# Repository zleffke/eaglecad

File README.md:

# eagle --OBSOLETE--
EagleCAD schematics, boards, and libraries

## --OBSOLETE--

The projects in this repository have been moved to their own stand alone repositories.  Finally decided it was dumb to have everything in one repo, because if anyone else actually wants to use one thing, they would have to clone everything.

The files in this repo will no longer be updated and new projects will be created in their own repo.  This repo is not being nuked for the moment and is being kept around as an archival repo in case I forgot to move something over to its own repo.  Eventually, this will get nuked.

## -------------

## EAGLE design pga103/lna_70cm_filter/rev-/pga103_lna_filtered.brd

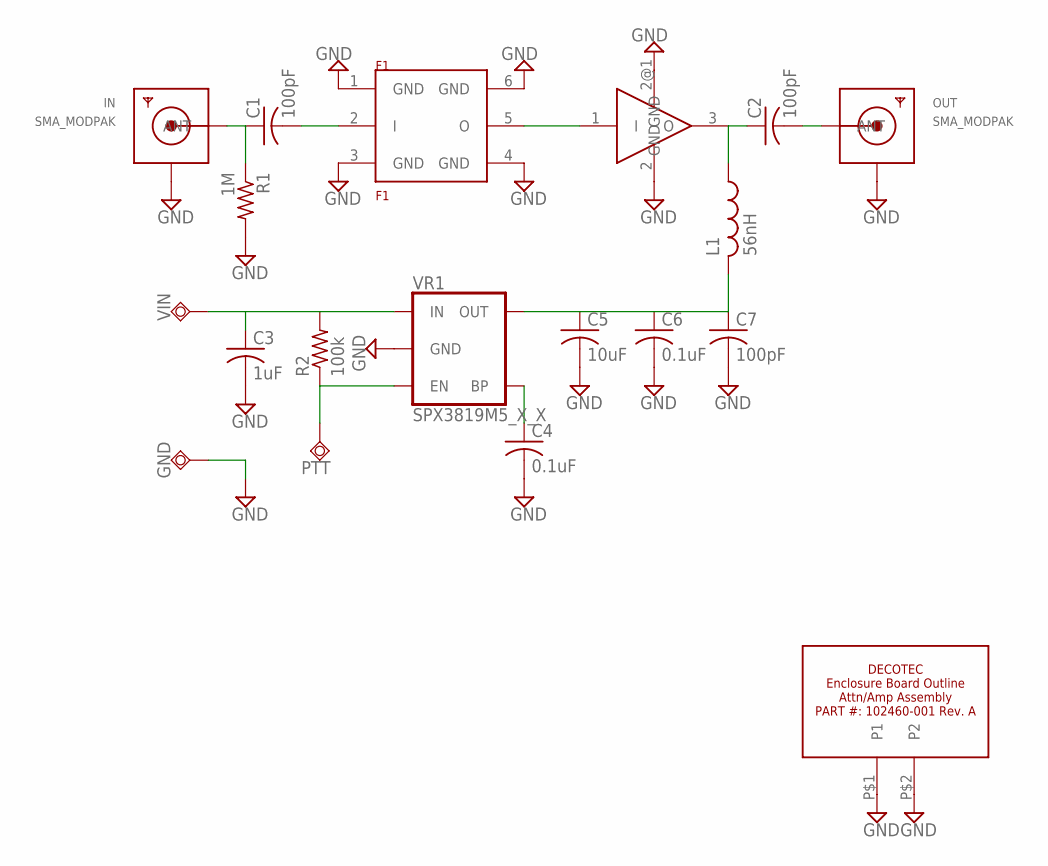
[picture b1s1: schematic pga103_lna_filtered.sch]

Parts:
A1: PGA-103+; SOT89
C1, C2, C7: 100pF; C0805K
C3: 1uF; C0805K
C4, C6: 0.1uF; C0805K
C5: 10uF; C0805K
F1: F1; SM3030-6
GND: TPSQTP20SQ; TP20SQ
IN: SMA_MODPAK; SMA_MODPAK_V1
L1: 56nH; C0805K
OUT: SMA_MODPAK; SMA_MODPAK_V1
PTT: TPSQTP20SQ; TP20SQ
R1: 1M; R0805
R2: 100k; R0805
U$1: DECOTEC_102460-001A
VIN: TPSQTP20SQ; TP20SQ
VR1: SPX3819M5_X_X; SOT23-5

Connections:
GND: A1.2 (GND), A1.2@1 (GND), C3.2, C4.2, C5.2, C6.2, C7.2, F1.1 (GND), F1.3 (GND), F1.4 (GND), F1.6 (GND), GND.TP, IN.GND@1 (GND1), OUT.GND@1 (GND1), R1.2, U$1.P$1 (P1), U$1.P$2 (P2), VR1.2 (GND)
unnamed: C1.1, IN.P (ANT), R1.1
unnamed: C1.2, F1.2 (I)
unnamed: C2.2, OUT.P (ANT)
unnamed: A1.3 (O), C2.1, L1.1
unnamed: A1.1 (I), F1.5 (O)
unnamed: C5.1, C6.1, C7.1, L1.2, VR1.5 (OUT)
unnamed: C4.1, VR1.4 (BP)
PTT: PTT.TP, R2.1, VR1.3 (EN)
VIN: C3.1, R2.2, VIN.TP, VR1.1 (IN)

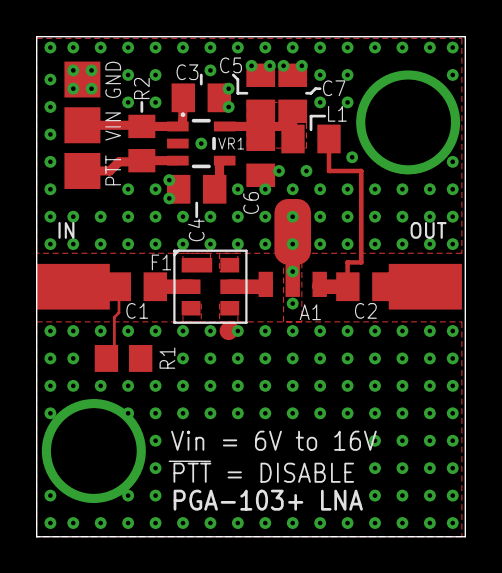
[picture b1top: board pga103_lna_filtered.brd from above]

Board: 2 copper layers, 23.8 x 27.8 mm, 19 parts (0 on the bottom side), 10 nets.

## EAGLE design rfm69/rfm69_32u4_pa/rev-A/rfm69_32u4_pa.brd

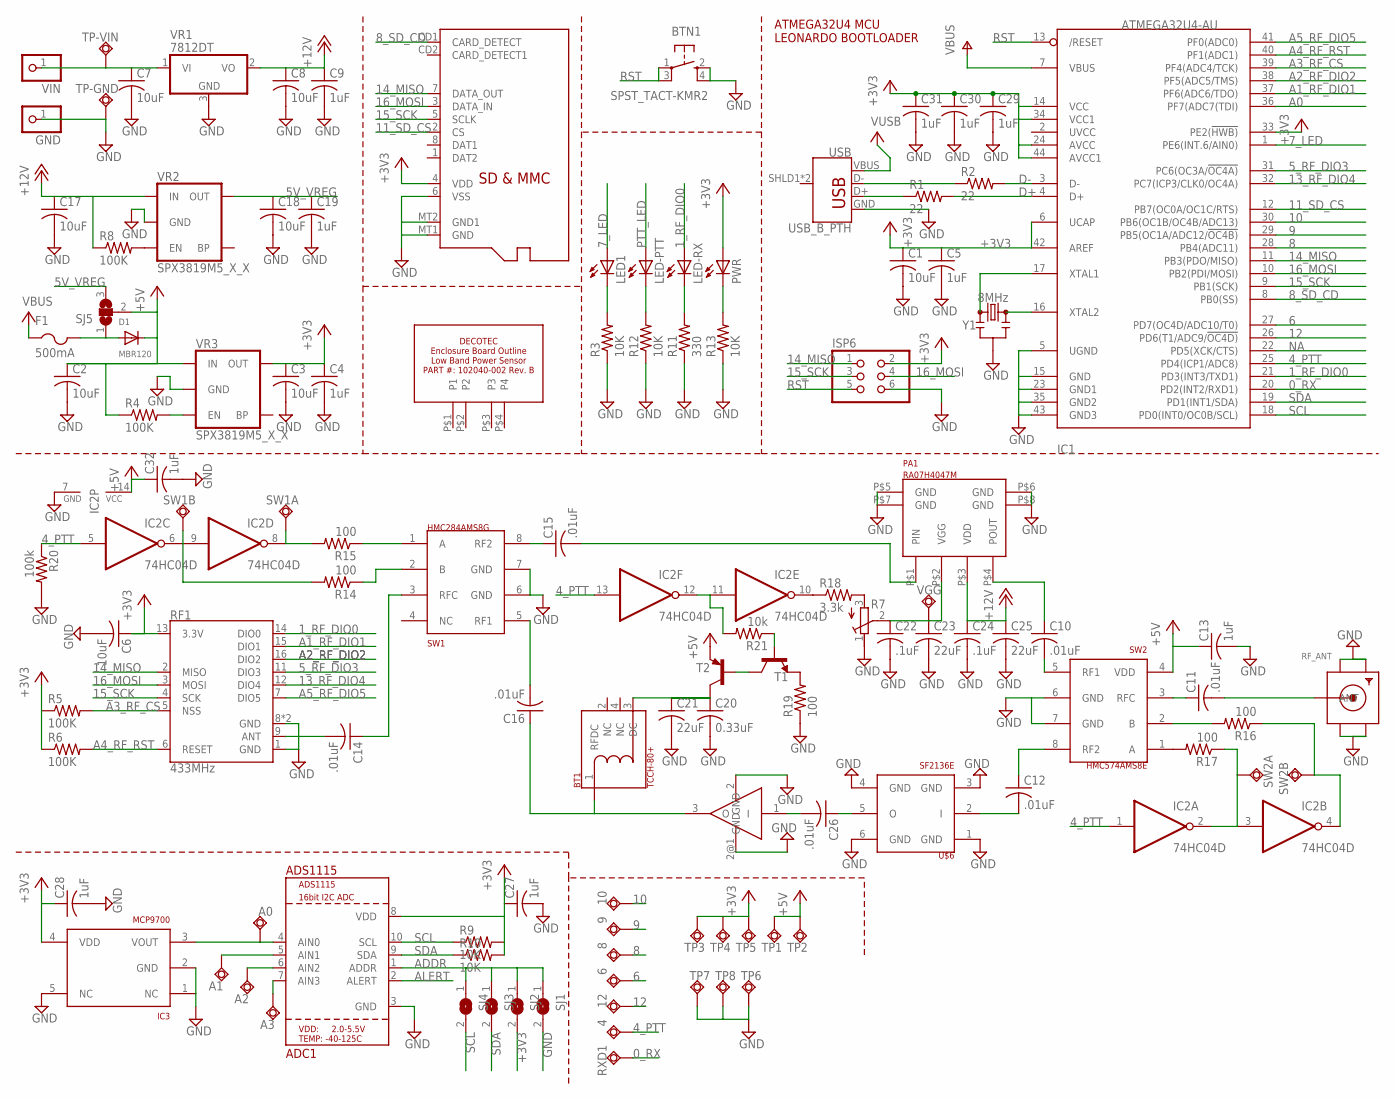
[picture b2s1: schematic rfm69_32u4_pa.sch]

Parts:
4, 6, 8, 9, 10, 12: TPSQTP10SQ; TP10SQ
A0, A1, A2, A3: TPSQTP10SQ; TP10SQ
ADC1: ADS1115; MSOP10
BT1: TCCH-80+
BTN1: SPST_TACT-KMR2; KMR2
C1, C2, C3, C6, C7, C8, C17, C18: 10uF; C0805K
C4, C5, C9, C13, C19, C27, C28, C29, C30, C31, C32: 1uF; C0805K
C10, C11, C12, C14, C15, C16, C26: .01uF; C0805K
C20: 0.33uF; C0805K
C21, C23, C25: 22uF; C0805K
C22, C24: .1uF; C0805K
D1: MBR120; SOD-123
F1: 500mA; R1206
GND: PINHD-1X1; 1X01
IC1: ATMEGA32U4-AU; TQFP44
IC2: 74HC04D; SO14
IC3: MCP9700; SC70
ISP6: PINHD-2X3; 2X03
LED1: LEDCHIPLED_0805; CHIPLED_0805
LED-PTT: LEDCHIPLED_0805; CHIPLED_0805
LED-RX: LEDCHIPLED_0805; CHIPLED_0805
PA1: RA07H4047M; H46
PGA-103+: PGA-103+; SOT89
PWR: LEDCHIPLED_0805; CHIPLED_0805
R1, R2: 22; R0805
R3, R9, R10, R12, R13: 10K; R0805
R4, R5, R6, R8: 100K; R0805
R7: R-TRIMM3314G; RTRIM3314G
R11: 330; R0805
R14, R15, R16, R17, R19: 100; R0805
R18: 3.3k; R0805
R20: 100k; R0805
R21: 10k; R0805
RF1: 433MHz; RFM69HCW-XXXS2
RF_ANT: SMACONNECTOR_EDGE; SMA_EDGELAUNCH
RXD1: TPSQTP10SQ; TP10SQ
SJ1, SJ2, SJ3, SJ4: SJ
SJ5: SJ2W; SJ_2
SW1: HMC284AMS8G; MSOP8
SW1A, SW1B, SW2A, SW2B: TPSQTP10SQ; TP10SQ
SW2: HMC574AMS8E; MSOP8
T1: MMBT3904LT1-NPN-SOT23-BEC; SOT23-BEC
T2: MMBT3906LT1-PNP-SOT23-BEC; SOT23-BEC
TP1, TP2, TP3, TP4, TP5, TP6, TP7, TP8: TPSQTP10SQ; TP10SQ
TP-GND: TPSQTP20SQ; TP20SQ
TP-VIN: TPSQTP20SQ; TP20SQ
U$2: DECOTEC_102040-002B
U$3: MICROSD
U$6: SF2136E; SM3030-6
USB: USB_B_PTH; USB-B-PTH
VGG: TPSQTP10SQ; TP10SQ
VIN: PINHD-1X1; 1X01
VR1: 7812DT; TO252
VR2, VR3: SPX3819M5_X_X; SOT23-5
Y1: 8MHz; RESONATOR-SMD-3.2X1.3

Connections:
0_RX: IC1.20 (PD2(INT2/RXD1)), RXD1.TP
1_RF_DIO0: IC1.21 (PD3(INT3/TXD1)), LED-RX.A, RF1.14 (DIO0)
4_PTT: 4.TP, IC1.25 (PD4(ICP1/ADC8)), IC2.1 (I), IC2.5 (I), IC2.13 (I), R20.1
5V_VREG: C18.1, C19.1, SJ5.3, VR2.5 (OUT)
5_RF_DIO3: IC1.31 (PC6(OC3A/!OC4A)), RF1.11 (DIO3)
6: 6.TP, IC1.27 (PD7(OC4D/ADC10/T0))
7_LED: IC1.1 (PE6(INT.6/AIN0)), LED1.A
8: 8.TP, IC1.28 (PB4(ADC11))
8_SD_CD: IC1.8 (PB0(SS)), U$3.CD1 (CARD_DETECT)
9: 9.TP, IC1.29 (PB5(OC1A/ADC12/!OC4B))
10: 10.TP, IC1.30 (PB6(OC1B/OC4B/ADC13))
11_SD_CS: IC1.12 (PB7(OC0A/OC1C/RTS)), U$3.2 (CS)
12: 12.TP, IC1.26 (PD6(T1/ADC9/!OC4D))
13_RF_DIO4: IC1.32 (PC7(ICP3/CLK0/OC4A)), RF1.12 (DIO4)
14_MISO: IC1.11 (PB3(PDO/MISO)), ISP6.1, RF1.2 (MISO), U$3.7 (DATA_OUT)
15_SCK: IC1.9 (PB1(SCK)), ISP6.3, RF1.4 (SCK), U$3.5 (SCLK)
16_MOSI: IC1.10 (PB2(PDI/MOSI)), ISP6.4, RF1.3 (MOSI), U$3.3 (DATA_IN)
+3V3: ADC1.8 (VDD), C1.1, C3.1, C4.1, C5.1, C6.1, C27.1, C28.1, C29.1, C30.1, C31.1, IC1.6 (UCAP), IC1.14 (VCC), IC1.24 (AVCC), IC1.33 (PE2(!HWB)), IC1.34 (VCC1), IC1.42 (AREF), IC1.44 (AVCC1), IC3.4 (VDD), ISP6.2, PWR.A, R5.1, R6.1, R9.2, R10.2, RF1.13 (3.3V), SJ2.2, TP3.TP, TP4.TP, TP5.TP, U$3.4 (VDD), VR3.5 (OUT)
+5V: C2.1, C13.1, C32.1, D1.C, IC2.14 (VCC), R4.1, SJ5.2, SW2.4 (VDD), T2.E, TP1.TP, TP2.TP, VR3.1 (IN)
+12V: C8.1, C9.1, C17.1, C24.1, C25.1, PA1.P$3 (VDD), R8.1, VR1.2 (VO), VR2.1 (IN)
A0: IC1.36 (PF7(ADC7(TDI))
A1_RF_DIO1: IC1.37 (PF6(ADC6/TDO)), RF1.15 (DIO1)
A2_RF_DIO2: IC1.38 (PF5(ADC5/TMS)), RF1.16 (DIO2)
A3_RF_CS: IC1.39 (PF4(ADC4/TCK)), R5.2, RF1.5 (NSS)
A4_RF_RST: IC1.40 (PF1(ADC1)), R6.2, RF1.6 (RESET)
A5_RF_DIO5: IC1.41 (PF0(ADC0)), RF1.7 (DIO5)
ADDR: ADC1.1 (ADDR), SJ1.1, SJ2.1, SJ3.1, SJ4.1
AIN1: A1.TP, ADC1.5 (AIN1)
AIN2: A2.TP, ADC1.6 (AIN2)
AIN3: A3.TP, ADC1.7 (AIN3)
ALERT: ADC1.2 (ALERT)
ANT: C14.2, RF1.9 (ANT)
D+: IC1.4 (D+), R1.2
D-: IC1.3 (D-), R2.2
EN: R4.2, VR3.3 (EN)
GND: ADC1.3 (GND), BTN1.2 (S), BTN1.4 (S1), C1.2, C2.2, C3.2, C4.2, C5.2, C6.2, C7.2, C8.2, C9.2, C13.2, C17.2, C18.2, C19.2, C20.2, C21.2, C22.2, C23.2, C24.2, C25.2, C27.2, C28.2, C29.2, C30.2, C31.2, C32.2, GND.1, IC1.5 (UGND), IC1.15 (GND), IC1.23 (GND1), IC1.35 (GND2), IC1.43 (GND3), IC2.7 (GND), IC3.1 (NC), IC3.2 (GND), IC3.5 (NC), ISP6.6, PA1.P$5 (GND), PA1.P$6 (GND), PA1.P$7 (GND), PA1.P$8 (GND), PGA-103+.2 (GND), PGA-103+.2@1 (GND), R3.1, R7.1 (E), R11.1, R12.1, R13.1, R19.1, R20.2, RF1.1 (GND), RF1.8 (GND), RF1.10 (GND), RF_ANT.GND@1 (GND4), RF_ANT.GND@2 (GND3), RF_ANT.GND@3 (GND2), RF_ANT.GND@4 (GND1), SJ1.2, SW1.6 (GND), SW1.7 (GND), SW2.6 (GND), SW2.7 (GND), TP6.TP, TP7.TP, TP8.TP, TP-GND.TP, U$3.6 (VSS), U$3.MT1 (GND), U$3.MT2 (GND1), U$6.1 (GND), U$6.3 (GND), U$6.4 (GND), U$6.6 (GND), USB.GND, VR1.3 (GND), VR2.2 (GND), VR3.2 (GND), Y1.2
unnamed: R1.1, USB.D+
unnamed: LED1.C, R3.2
unnamed: R2.1, USB.D-
unnamed: C15.2, PA1.P$1 (PIN)
unnamed: C10.1, PA1.P$4 (POUT)
unnamed: C10.2, SW2.5 (RF1)
unnamed: LED-PTT.C, R12.2
unnamed: PWR.C, R13.2
unnamed: C26.1, U$6.5 (O)
unnamed: C11.2, RF_ANT.P (ANT)
unnamed: C11.1, SW2.3 (RFC)
unnamed: C14.1, SW1.3 (RFC)
unnamed: C15.1, SW1.8 (RF2)
unnamed: C16.2, SW1.5 (RF1)
unnamed: R14.1, SW1.2 (B)
unnamed: BT1.1 (RFDC), C16.1, PGA-103+.3 (O)
unnamed: C22.1, C23.1, PA1.P$2 (VGG), R7.2 (S), VGG.TP
unnamed: C12.1, SW2.8 (RF2)
unnamed: C12.2, U$6.2 (I)
unnamed: R15.1, SW1.1 (A)
unnamed: C26.2, PGA-103+.1 (I)
unnamed: R8.2, VR2.3 (EN)
unnamed: LED-RX.C, R11.2
unnamed: R17.2, SW2.1 (A)
unnamed: R16.2, SW2.2 (B)
unnamed: IC2.11 (I), IC2.12 (O), R21.2
unnamed: R7.3 (A), R18.2
unnamed: T1.C, T2.B
unnamed: BT1.3 (DC), C20.1, C21.1, T2.C
unnamed: R19.2, T1.E
unnamed: R21.1, T1.B
NA: IC1.22 (PD5(XCK/CTS))
PTT_LED: IC2.10 (O), LED-PTT.A, R18.1
RST: BTN1.1, BTN1.3 (P1), IC1.13 (/RESET), ISP6.5
SCL: ADC1.10 (SCL), IC1.18 (PD0(INT0/OC0B/SCL)), R9.1, SJ4.2
SDA: ADC1.9 (SDA), IC1.19 (PD1(INT1/SDA)), R10.1, SJ3.2
SW1A: IC2.8 (O), R15.2, SW1A.TP
SW1B: IC2.6 (O), IC2.9 (I), R14.2, SW1B.TP
SW2A: IC2.2 (O), IC2.3 (I), R17.1, SW2A.TP
SW2B: IC2.4 (O), R16.1, SW2B.TP
VBUS: D1.A, F1.2, IC1.7 (VBUS), SJ5.1
VIN: C7.1, TP-VIN.TP, VIN.1, VR1.1 (VI)
VUSB: F1.1, USB.VBUS
V_PA_TEMP: A0.TP, ADC1.4 (AIN0), IC3.3 (VOUT)
XTAL1: IC1.17 (XTAL1), Y1.1
XTAL2: IC1.16 (XTAL2), Y1.3

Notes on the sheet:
ATMEGA32U4 MCU LEONARDO BOOTLOADER

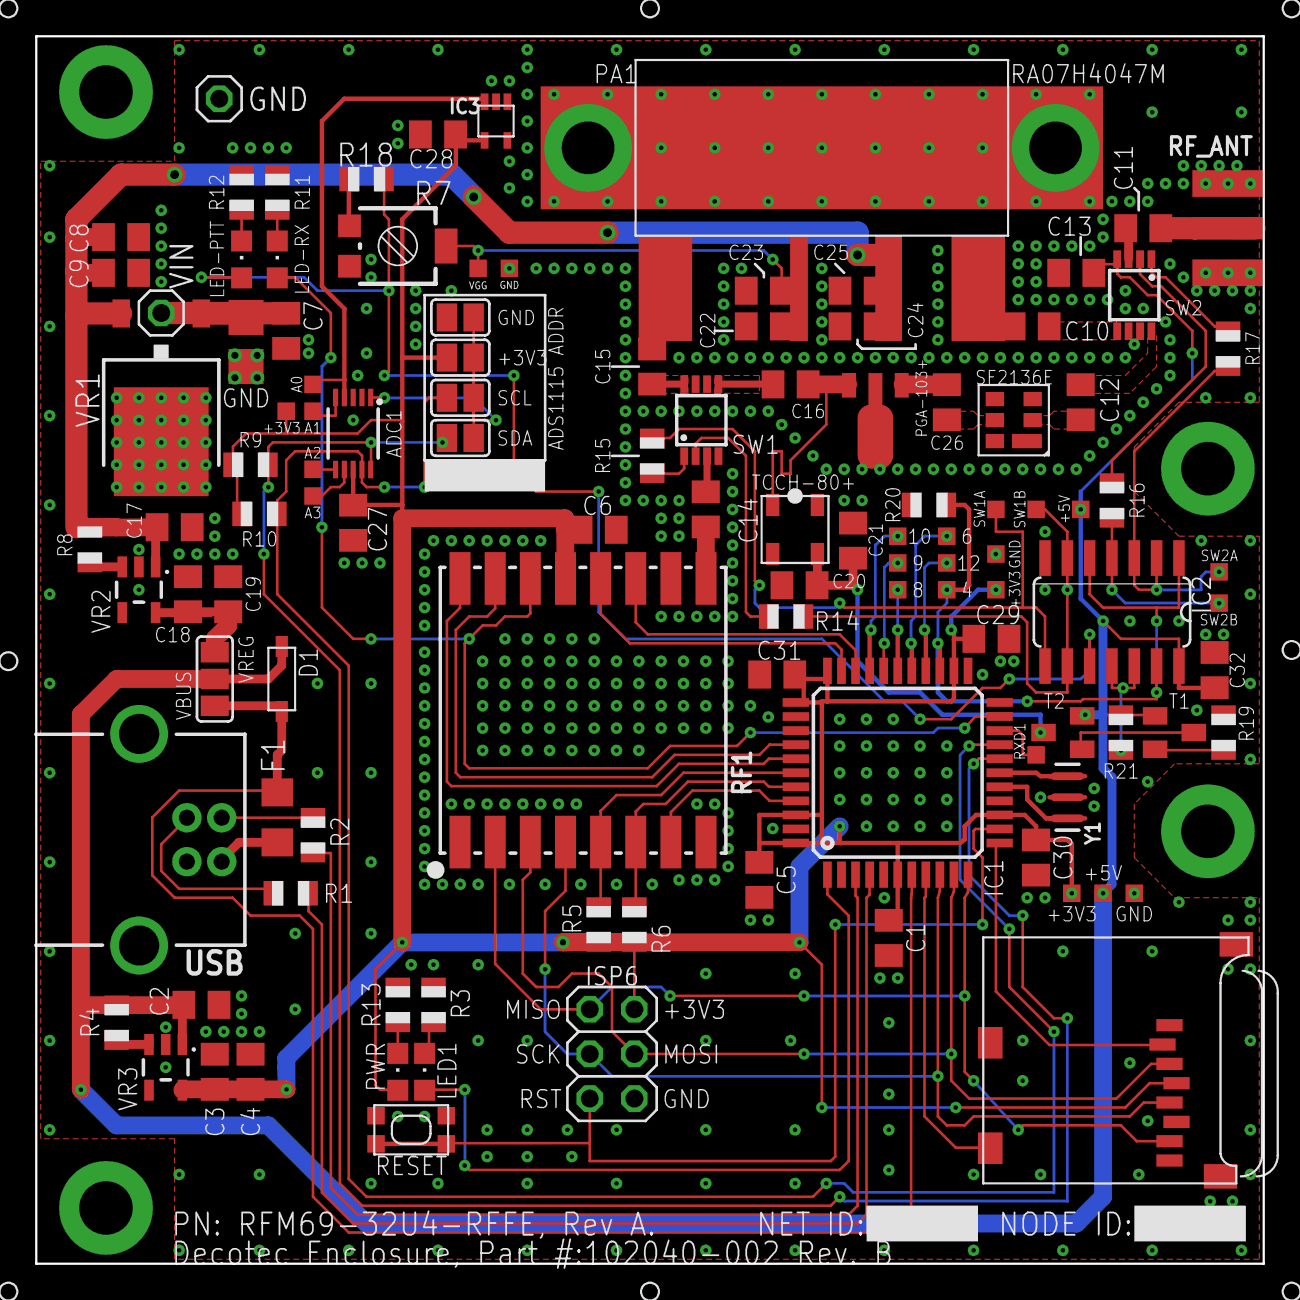
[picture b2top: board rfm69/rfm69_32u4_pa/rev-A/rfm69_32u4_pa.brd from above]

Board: 2 copper layers, 69.8 x 69.8 mm, 115 parts (0 on the bottom side), 79 nets.

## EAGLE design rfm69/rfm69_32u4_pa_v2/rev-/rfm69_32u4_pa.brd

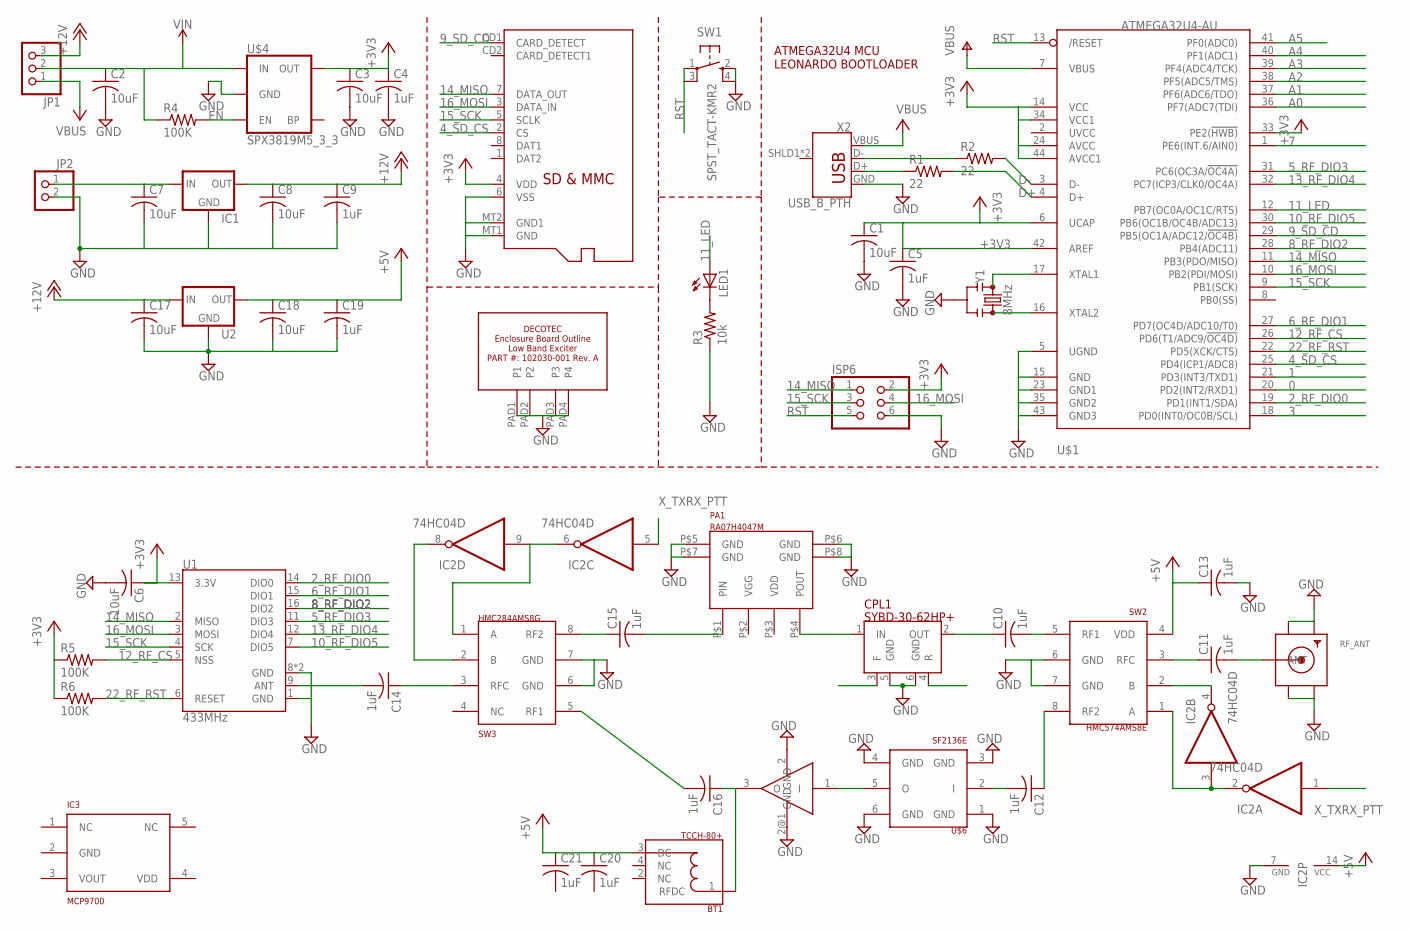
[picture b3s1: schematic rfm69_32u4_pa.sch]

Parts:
BT1: TCCH-80+
C1, C2, C3, C6, C7, C8, C17, C18: 10uF; C0805K
C4, C5, C9, C10, C11, C12, C13, C14, C15, C16, C19, C20, C21: 1uF; C0805K
CPL1: SYBD-30-62HP+
IC1: 78XXL
IC2: 74HC04D; SO14
IC3: MCP9700; SC70
ISP6: PINHD-2X3; 2X03
JP1: PINHD-1X3; 1X03
JP2: PINHD-1X2; 1X02
LED1: LEDCHIPLED_0805; CHIPLED_0805
PA1: RA07H4047M; H46
R1, R2: 22; R0805
R3: 10k; R0805
R4, R5, R6: 100K; R0805
RF_ANT: SMACONNECTOR_EDGE; SMA_EDGELAUNCH
SW1: SPST_TACT-KMR2; KMR2
SW2: HMC574AMS8E; MSOP8
SW3: HMC284AMS8G; MSOP8
U1: 433MHz; RFM69HCW-XXXS2
U2: V_REG_78XX-TO-220; TO-220-ALT
U$1: ATMEGA32U4-AU; TQFP44
U$2: DECOTEC_102030-001A
U$3: MICROSD
U$4: SPX3819M5_3_3; SOT23-5
U$5: PGA-103+; SOT89
U$6: SF2136E; SM3030-6
X2: USB_B_PTH; USB-B-PTH
Y1: 8MHz; RESONATOR-SMD-3.2X1.3

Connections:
0: U$1.20 (PD2(INT2/RXD1))
1: U$1.21 (PD3(INT3/TXD1))
2_RF_DIO0: U1.14 (DIO0), U$1.19 (PD1(INT1/SDA))
3: U$1.18 (PD0(INT0/OC0B/SCL))
4_SD_CS: U$1.25 (PD4(ICP1/ADC8)), U$3.2 (CS)
5_RF_DIO3: U1.11 (DIO3), U$1.31 (PC6(OC3A/!OC4A))
6_RF_DIO1: U1.15 (DIO1), U$1.27 (PD7(OC4D/ADC10/T0))
7: U$1.1 (PE6(INT.6/AIN0))
8_RF_DIO2: U1.16 (DIO2), U$1.28 (PB4(ADC11))
9_SD_CD: U$1.29 (PB5(OC1A/ADC12/!OC4B)), U$3.CD1 (CARD_DETECT)
10_RF_DIO5: U1.7 (DIO5), U$1.30 (PB6(OC1B/OC4B/ADC13))
11_LED: LED1.A, U$1.12 (PB7(OC0A/OC1C/RTS))
12_RF_CS: R5.2, U1.5 (NSS), U$1.26 (PD6(T1/ADC9/!OC4D))
13_RF_DIO4: U1.12 (DIO4), U$1.32 (PC7(ICP3/CLK0/OC4A))
14_MISO: ISP6.1, U1.2 (MISO), U$1.11 (PB3(PDO/MISO)), U$3.7 (DATA_OUT)
15_SCK: ISP6.3, U1.4 (SCK), U$1.9 (PB1(SCK)), U$3.5 (SCLK)
16_MOSI: ISP6.4, U1.3 (MOSI), U$1.10 (PB2(PDI/MOSI)), U$3.3 (DATA_IN)
22_RF_RST: R6.2, U1.6 (RESET), U$1.22 (PD5(XCK/CTS))
+3V3: C1.1, C3.1, C4.1, C5.1, C6.1, ISP6.2, R5.1, R6.1, U1.13 (3.3V), U$1.6 (UCAP), U$1.14 (VCC), U$1.24 (AVCC), U$1.33 (PE2(!HWB)), U$1.34 (VCC1), U$1.42 (AREF), U$1.44 (AVCC1), U$3.4 (VDD), U$4.5 (OUT)
+5V: BT1.3 (DC), C13.1, C18.1, C19.1, C20.1, C21.1, IC2.14 (VCC), SW2.4 (VDD), U2.OUT
+12V: C8.1, C9.1, C17.1, IC1.OUT, JP1.3, U2.IN
A0: U$1.36 (PF7(ADC7(TDI))
A1: U$1.37 (PF6(ADC6/TDO))
A2: U$1.38 (PF5(ADC5/TMS))
A3: U$1.39 (PF4(ADC4/TCK))
A4: U$1.40 (PF1(ADC1))
A5: U$1.41 (PF0(ADC0))
ANT: C14.2, U1.9 (ANT)
CPL_FWD: CPL1.3 (F)
CPL_REV: CPL1.4 (R)
D+: R1.2, U$1.4 (D+)
D-: R2.2, U$1.3 (D-)
EN: R4.2, U$4.3 (EN)
GND: C1.2, C2.2, C3.2, C4.2, C5.2, C6.2, C7.2, C8.2, C9.2, C13.2, C17.2, C18.2, C19.2, CPL1.5 (GND), CPL1.6 (GND), IC1.GND, IC2.7 (GND), ISP6.6, JP2.2, PA1.P$5 (GND), PA1.P$6 (GND), PA1.P$7 (GND), PA1.P$8 (GND), R3.1, RF_ANT.GND@1 (GND4), RF_ANT.GND@2 (GND3), RF_ANT.GND@3 (GND2), RF_ANT.GND@4 (GND1), SW1.2 (S), SW1.4 (S1), SW2.6 (GND), SW2.7 (GND), SW3.6 (GND), SW3.7 (GND), U1.1 (GND), U1.8 (GND), U1.10 (GND), U2.GND, U$1.5 (UGND), U$1.15 (GND), U$1.23 (GND1), U$1.35 (GND2), U$1.43 (GND3), U$2.PAD1 (P1), U$2.PAD2 (P2), U$2.PAD3 (P3), U$2.PAD4 (P4), U$3.6 (VSS), U$3.MT1 (GND), U$3.MT2 (GND1), U$4.2 (GND), U$5.2 (GND), U$5.2@1 (GND), U$6.1 (GND), U$6.3 (GND), U$6.4 (GND), U$6.6 (GND), X2.GND, Y1.2
unnamed: R1.1, X2.D+
unnamed: LED1.C, R3.2
unnamed: R2.1, X2.D-
unnamed: C10.2, SW2.5 (RF1)
unnamed: C7.1, IC1.IN, JP2.1
unnamed: C12.1, SW2.8 (RF2)
unnamed: IC2.2 (O), IC2.3 (I), SW2.1 (A)
unnamed: IC2.4 (O), SW2.2 (B)
unnamed: U$5.1 (I), U$6.5 (O)
unnamed: C11.2, RF_ANT.P (ANT)
unnamed: C11.1, SW2.3 (RFC)
unnamed: C14.1, SW3.3 (RFC)
unnamed: C15.1, SW3.8 (RF2)
unnamed: C15.2, PA1.P$1 (PIN)
unnamed: IC2.6 (O), IC2.9 (I), SW3.1 (A)
unnamed: BT1.1 (RFDC), C16.1, U$5.3 (O)
unnamed: IC2.8 (O), SW3.2 (B)
unnamed: C16.2, SW3.5 (RF1)
unnamed: C12.2, U$6.2 (I)
RF_IN: CPL1.1 (IN), PA1.P$4 (POUT)
RF_OUT: C10.1, CPL1.2 (OUT)
RST: ISP6.5, SW1.1, SW1.3 (P1), U$1.13 (/RESET)
VBUS: JP1.1, U$1.7 (VBUS), X2.VBUS
VIN: C2.1, JP1.2, R4.1, U$4.1 (IN)
XTAL1: U$1.17 (XTAL1), Y1.1
XTAL2: U$1.16 (XTAL2), Y1.3
X_TXRX_PTT: IC2.1 (I), IC2.5 (I)

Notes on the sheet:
ATMEGA32U4 MCU LEONARDO BOOTLOADER

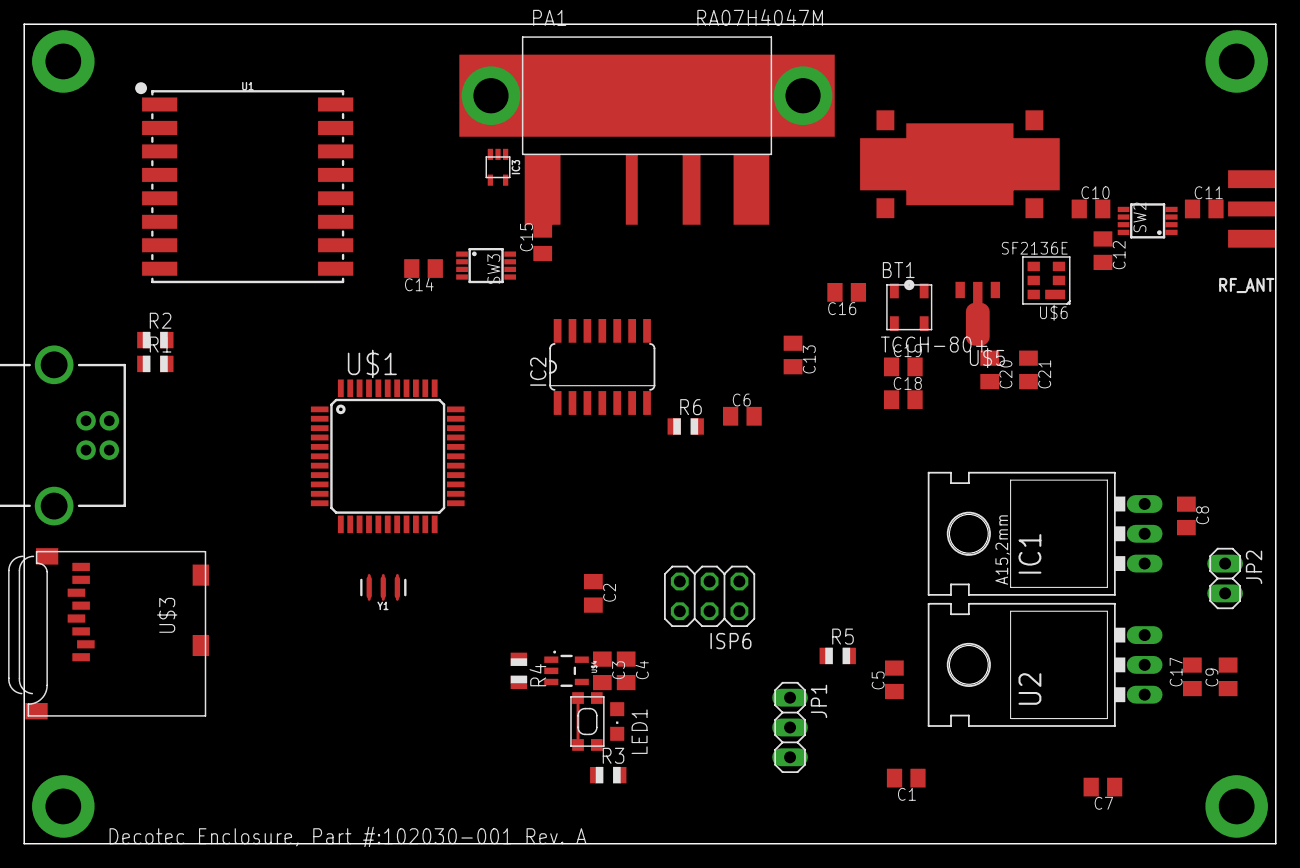
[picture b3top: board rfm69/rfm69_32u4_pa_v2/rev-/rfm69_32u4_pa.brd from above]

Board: 2 copper layers, 106.7 x 69.8 mm, 51 parts (0 on the bottom side), 49 nets.

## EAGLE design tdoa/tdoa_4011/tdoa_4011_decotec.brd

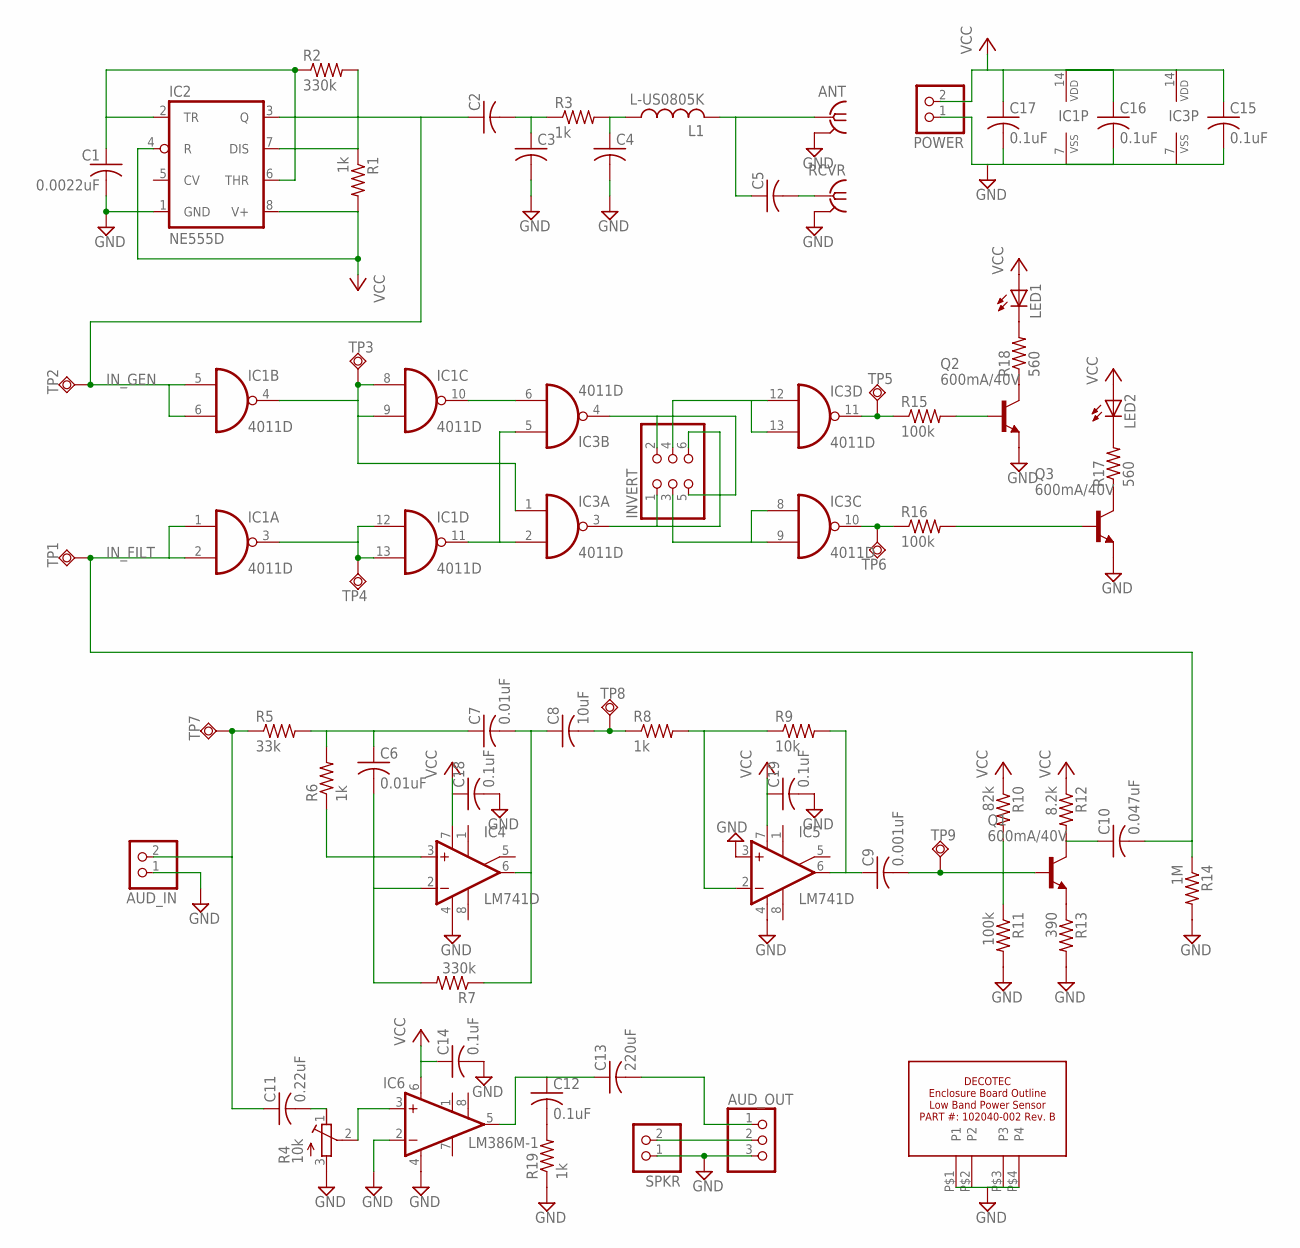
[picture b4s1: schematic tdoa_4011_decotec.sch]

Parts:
ANT: SMA-142-0701-801/806; J502-ND-142-0701-801/806
AUD_IN: PINHD-1X2; 1X02
AUD_OUT: PINHD-1X3; 1X03
C1: 0.0022uF; C0805K
C2, C3, C4, C5: C-USC0805K; C0805K
C6, C7: 0.01uF; C0805K
C8: 10uF; C0805K
C9: 0.001uF; C0805K
C10: 0.047uF; C0805K
C11: 0.22uF; C0805K
C12, C14, C15, C16, C17, C18, C19: 0.1uF; C0805K
C13: 220uF; C0805K
IC1, IC3: 4011D; SO14
IC2: NE555D; SO08
IC4, IC5: LM741D; SO08
IC6: LM386M-1; SO08
INVERT: PINHD-2X3; 2X03
L1: L-US0805K; C0805K
LED1, LED2: LED3MM
POWER: PINHD-1X2; 1X02
Q1, Q2, Q3: 600mA/40V; SOT23-BEC
R1, R3, R6, R8, R19: 1k; R0805
R2, R7: 330k; R0805
R4: 10k; RTRIM3314G
R5: 33k; R0805
R9: 10k; R0805
R10: 82k; R0805
R11, R15, R16: 100k; R0805
R12: 8.2k; R0805
R13: 390; R0805
R14: 1M; R0805
R17, R18: 560; R0805
RCVR: SMA-142-0701-801/806; J502-ND-142-0701-801/806
SPKR: PINHD-1X2; 1X02
TP1, TP2, TP3, TP4, TP5, TP6, TP7, TP8, TP9: TPSQTP20SQ; TP20SQ
U$1: DECOTEC_102040-002B

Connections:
AUDIO_IN: AUD_IN.2, C11.1, R5.1, TP7.TP
GND: ANT.G@1 (2), ANT.G@2 (2), ANT.G@3 (2), ANT.G@4 (2), AUD_IN.1, AUD_OUT.3, C1.2, C3.2, C4.2, C14.2, C15.2, C16.2, C17.2, C18.2, C19.2, IC1.7 (VSS), IC2.1 (GND), IC3.7 (VSS), IC4.4 (V-), IC5.3 (+IN), IC5.4 (V-), IC6.2 (-IN), IC6.4 (GND), POWER.1, Q2.E, Q3.E, R4.3 (A), R11.2, R13.2, R14.2, R19.1, RCVR.G@1 (2), RCVR.G@2 (2), RCVR.G@3 (2), RCVR.G@4 (2), SPKR.1, U$1.P$1 (P1), U$1.P$2 (P2), U$1.P$3 (P3), U$1.P$4 (P4)
IN_FILT: C10.2, IC1.1 (I0), IC1.2 (I1), R14.1, TP1.TP
IN_GEN: C2.1, IC1.5 (I0), IC1.6 (I1), IC2.3 (Q), TP2.TP
unnamed: IC1.4 (O), IC1.8 (I0), IC1.9 (I1), IC3.1 (I0), TP3.TP
unnamed: IC2.7 (DIS), R1.1, R2.2
unnamed: C1.1, IC2.2 (TR), IC2.6 (THR), R2.1
unnamed: C2.2, C3.1, R3.1
unnamed: C4.1, L1.1, R3.2
unnamed: AUD_OUT.1, C13.2
unnamed: C5.2, RCVR.1
unnamed: ANT.1, C5.1, L1.2
unnamed: C6.1, C7.1, R5.2, R6.2
unnamed: IC4.3 (+IN), R6.1
unnamed: C6.2, IC4.2 (-IN), R7.2
unnamed: C7.2, C8.1, IC4.6 (OUT), R7.1
unnamed: C8.2, R8.1, TP8.TP
unnamed: IC5.2 (-IN), R8.2, R9.1
unnamed: C9.1, IC5.6 (OUT), R9.2
unnamed: C9.2, Q1.B, R10.2, R11.1, TP9.TP
unnamed: Q1.E, R13.1
unnamed: C10.1, Q1.C, R12.2
unnamed: IC1.3 (O), IC1.12 (I0), IC1.13 (I1), TP4.TP
unnamed: IC1.11 (O), IC3.2 (I1), IC3.5 (I0)
unnamed: IC3.4 (O), INVERT.2, INVERT.5
unnamed: IC1.10 (O), IC3.6 (I1)
unnamed: IC3.3 (O), INVERT.1, INVERT.6
unnamed: IC3.12 (I0), IC3.13 (I1), INVERT.4
unnamed: IC3.8 (I0), IC3.9 (I1), INVERT.3
unnamed: Q2.C, R18.1
unnamed: LED1.K (C), R18.2
unnamed: Q3.C, R17.1
unnamed: LED2.K (C), R17.2
unnamed: IC3.11 (O), R15.1, TP5.TP
unnamed: Q2.B, R15.2
unnamed: IC3.10 (O), R16.1, TP6.TP
unnamed: Q3.B, R16.2
unnamed: IC6.3 (+IN), R4.2 (S)
unnamed: C11.2, R4.1 (E)
unnamed: C12.1, C13.1, IC6.5 (OUT)
unnamed: C12.2, R19.2
SPKR+: AUD_OUT.2, SPKR.2
VCC: C14.1, C15.1, C16.1, C17.1, C18.1, C19.1, IC1.14 (VDD), IC2.4 (R), IC2.8 (V+), IC3.14 (VDD), IC4.7 (V+), IC5.7 (V+), IC6.6 (VS), LED1.A, LED2.A, POWER.2, R1.2, R10.1, R12.1

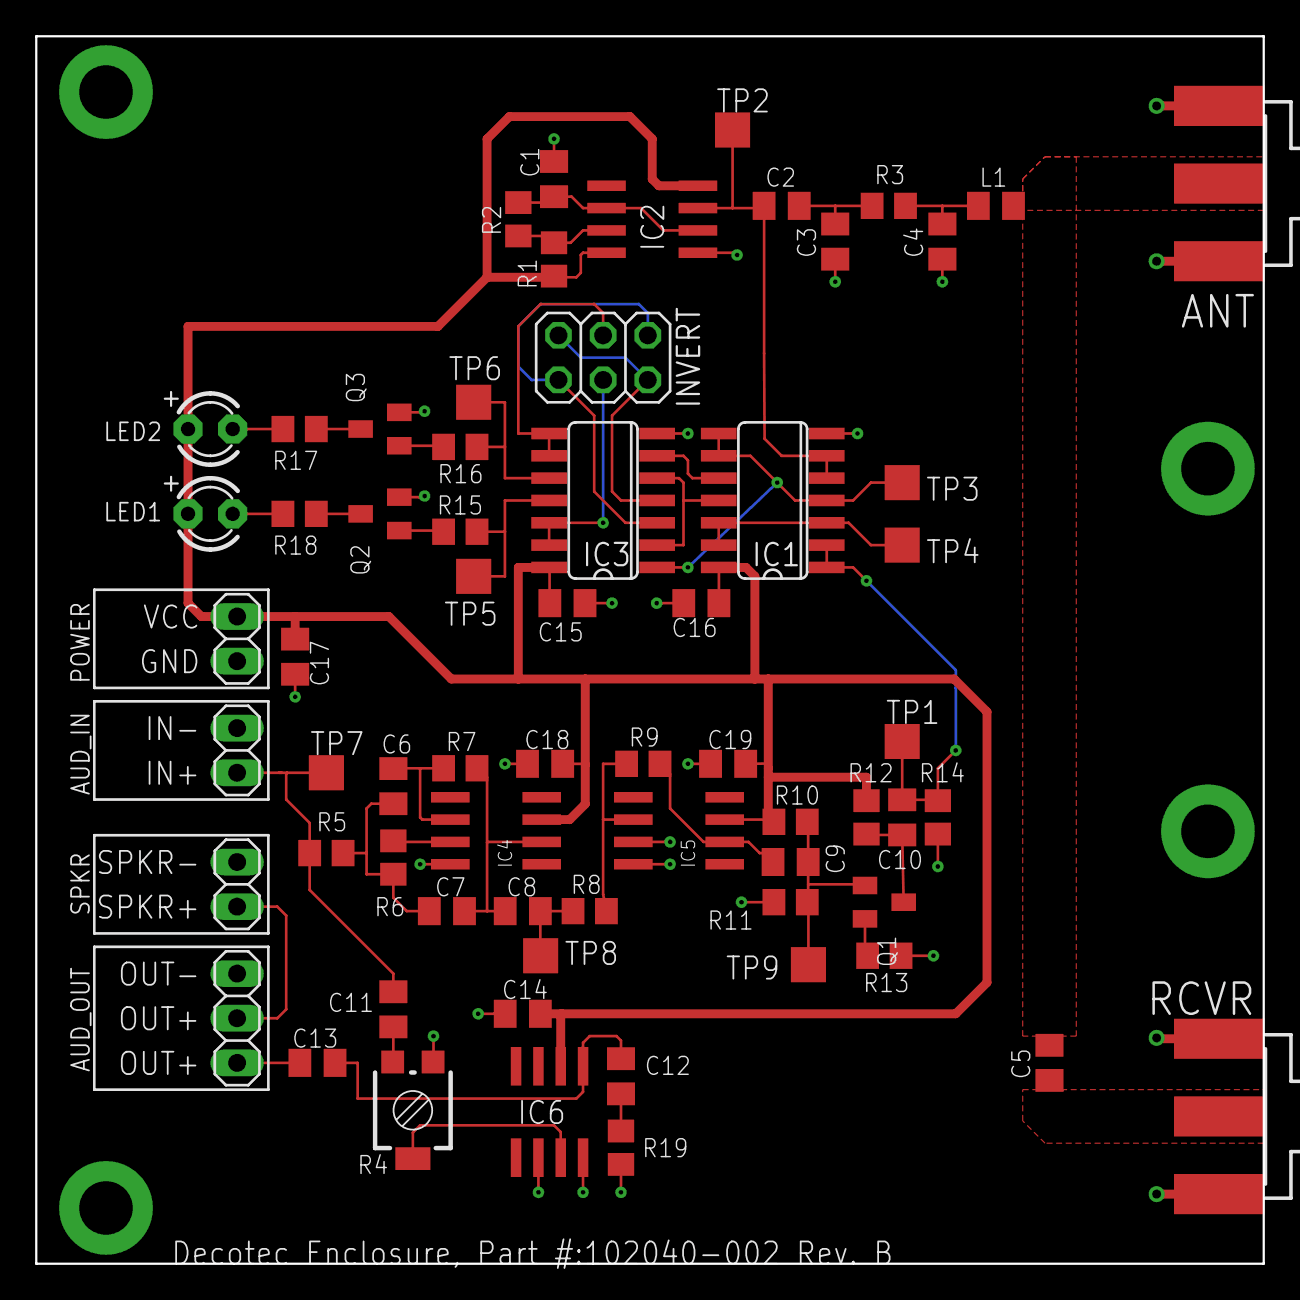
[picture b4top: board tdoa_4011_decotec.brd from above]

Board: 2 copper layers, 69.8 x 69.8 mm, 67 parts (0 on the bottom side), 43 nets.

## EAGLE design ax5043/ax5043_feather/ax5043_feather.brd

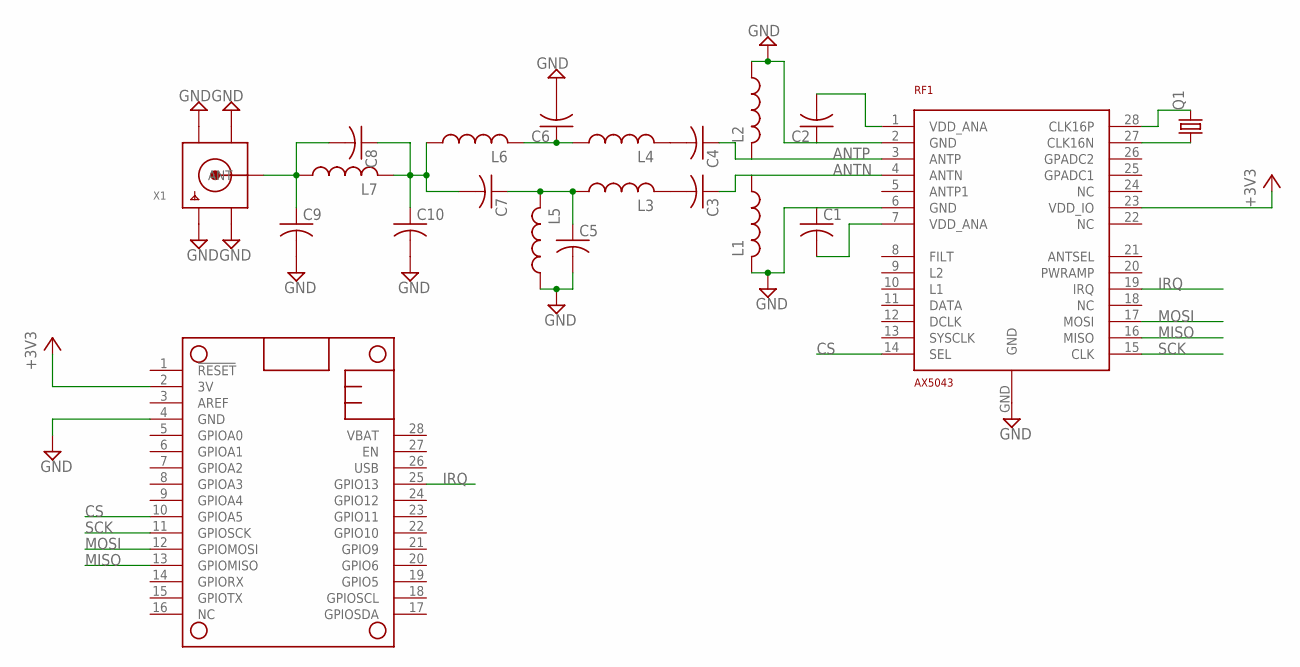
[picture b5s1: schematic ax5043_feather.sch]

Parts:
C1, C2, C3, C4, C5, C6, C7, C8, C9, C10: C-USC0603K; C0603K
L1, L2, L3, L4, L5, L6, L7: L-US0603K; C0603K
MS1: FEATHERWING
Q1: CRYSTALCTS406; CTS406
RF1: AX5043; QFN28-5X5
X1: SMACONNECTOR_EDGE_UFL; SMA_EDGELAUNCH_UFL

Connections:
+3V3: MS1.2 (3V), RF1.23 (VDD_IO)
ANTN: C3.1, L1.1, RF1.4 (ANTN)
ANTP: C4.1, L2.2, RF1.3 (ANTP)
CS: MS1.10 (GPIOA5), RF1.14 (SEL)
GND: C1.1, C2.1, C5.2, C6.2, C9.2, C10.2, L1.2, L2.1, L5.1, MS1.4 (GND), RF1.2 (GND), RF1.6 (GND), RF1.GND, X1.GND@1 (GND1), X1.GND@2 (GND2), X1.GND@3 (GND3), X1.GND@4 (GND4)
IRQ: MS1.25 (GPIO13), RF1.19 (IRQ)
MISO: MS1.13 (GPIOMISO), RF1.16 (MISO)
MOSI: MS1.12 (GPIOMOSI), RF1.17 (MOSI)
unnamed: C2.2, RF1.1 (VDD_ANA)
unnamed: Q1.3 (2), RF1.28 (CLK16P)
unnamed: Q1.1, RF1.27 (CLK16N)
unnamed: C1.2, RF1.7 (VDD_ANA)
unnamed: C4.2, L4.2
unnamed: C3.2, L3.2
unnamed: C5.1, C7.1, L3.1, L5.2
unnamed: C6.1, L4.1, L6.2
unnamed: C7.2, C8.1, C10.1, L6.1, L7.2
unnamed: C8.2, C9.1, L7.1, X1.P (ANT)
SCK: MS1.11 (GPIOSCK), RF1.15 (CLK)

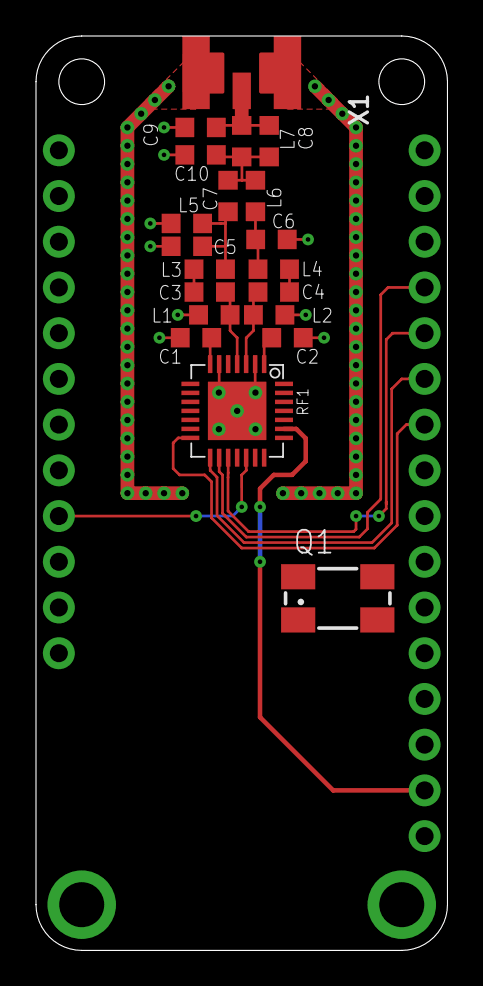
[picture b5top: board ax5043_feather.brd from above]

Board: 2 copper layers, 22.9 x 50.8 mm, 21 parts (0 on the bottom side), 19 nets.

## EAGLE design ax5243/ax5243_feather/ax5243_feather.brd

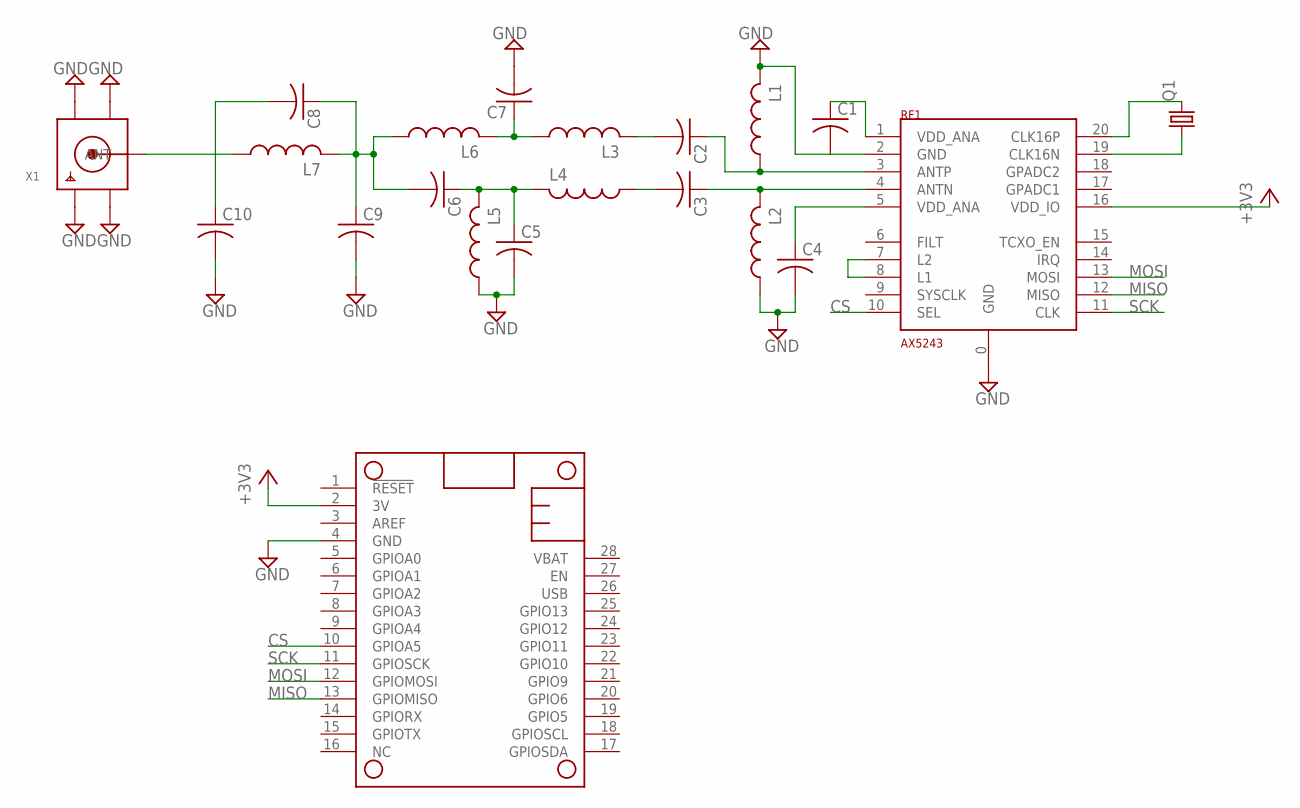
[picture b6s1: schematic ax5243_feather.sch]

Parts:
C1, C2, C3, C4, C5, C6, C7, C8, C9, C10: C-USC0805K; C0805K
L1, L2, L3, L4, L5, L6, L7: L-USL2012C; L2012C
MS1: FEATHERWING
Q1: CRYSTALCTS406; CTS406
RF1: AX5243; QFN20-4X4MM
X1: SMACONNECTOR_EDGE_UFL; SMA_EDGELAUNCH_UFL

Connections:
+3V3: MS1.2 (3V), RF1.16 (VDD_IO)
ANTN: C3.1, L2.2, RF1.4 (ANTN)
ANTP: C2.1, L1.1, RF1.3 (ANTP)
CS: MS1.10 (GPIOA5), RF1.10 (SEL)
GND: C1.2, C4.2, C5.2, C7.2, C9.2, C10.2, L1.2, L2.1, L5.1, MS1.4 (GND), RF1.0 (GND), RF1.2 (GND), X1.GND@1 (GND1), X1.GND@2 (GND2), X1.GND@3 (GND3), X1.GND@4 (GND4)
MISO: MS1.13 (GPIOMISO), RF1.12 (MISO)
MOSI: MS1.12 (GPIOMOSI), RF1.13 (MOSI)
unnamed: RF1.7 (L2), RF1.8 (L1)
unnamed: C4.1, RF1.5 (VDD_ANA)
unnamed: C1.1, RF1.1 (VDD_ANA)
unnamed: Q1.3 (2), RF1.20 (CLK16P)
unnamed: C3.2, L4.1
unnamed: C2.2, L3.2
unnamed: C5.1, C6.1, L4.2, L5.2
unnamed: Q1.1, RF1.19 (CLK16N)
unnamed: C6.2, C8.1, C9.1, L6.1, L7.2
unnamed: C7.1, L3.1, L6.2
unnamed: C8.2, C10.1, L7.1, X1.P (ANT)
SCK: MS1.11 (GPIOSCK), RF1.11 (CLK)

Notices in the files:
parts and their libraries:
SparkFun-RF: Licensing: Creative Commons ShareAlike 4.0 International - https://creativecommons.org/licenses/by-sa/4.0
